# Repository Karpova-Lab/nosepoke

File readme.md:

# Nosepoke

Full Documentation here: [https://karpova-lab.github.io/nosepoke/](https://karpova-lab.github.io/nosepoke/)

Ask questions here: [https://github.com/Karpova-Lab/nosepoke/discussions](https://github.com/Karpova-Lab/nosepoke/discussions)

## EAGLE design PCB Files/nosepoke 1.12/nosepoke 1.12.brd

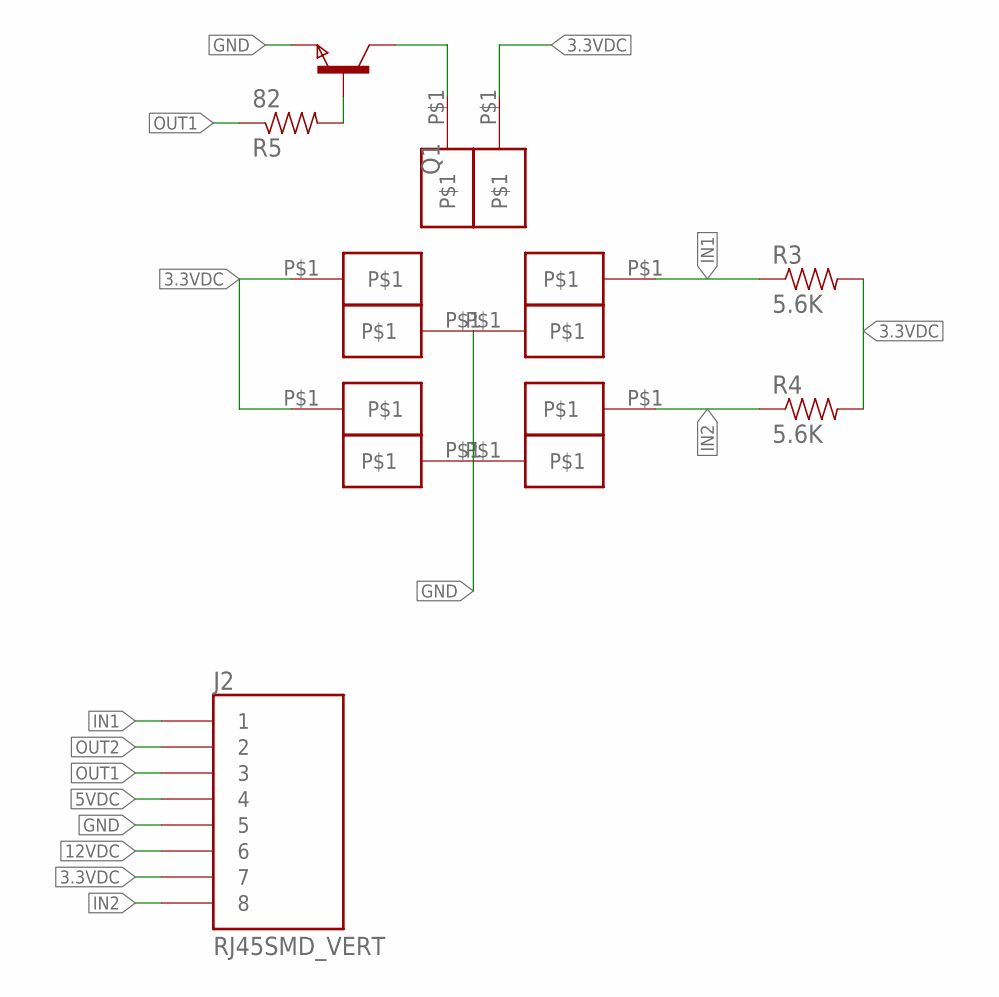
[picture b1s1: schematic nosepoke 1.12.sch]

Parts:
J2: RJ45SMD_VERT; RJ45_SMD_VERT
Q1: NPNSOT323; SOT323
R3, R4: 5.6K; 0805
R5: 82; 0805
U$1, U$2, U$3, U$4, U$5, U$6, U$7, U$8, U$9, U$10: PAD

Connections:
3.3VDC: J2.7, R3.2, R4.2, U$3.P$1, U$6.P$1, U$10.P$1
5VDC: J2.4
12VDC: J2.6
GND: J2.5, Q1.3 (E), U$1.P$1, U$2.P$1, U$5.P$1, U$8.P$1
IN1: J2.1, R3.1, U$7.P$1
IN2: J2.8, R4.1, U$4.P$1
unnamed: Q1.2 (B), R5.2
unnamed: Q1.1 (C), U$9.P$1
OUT1: J2.3, R5.1
OUT2: J2.2

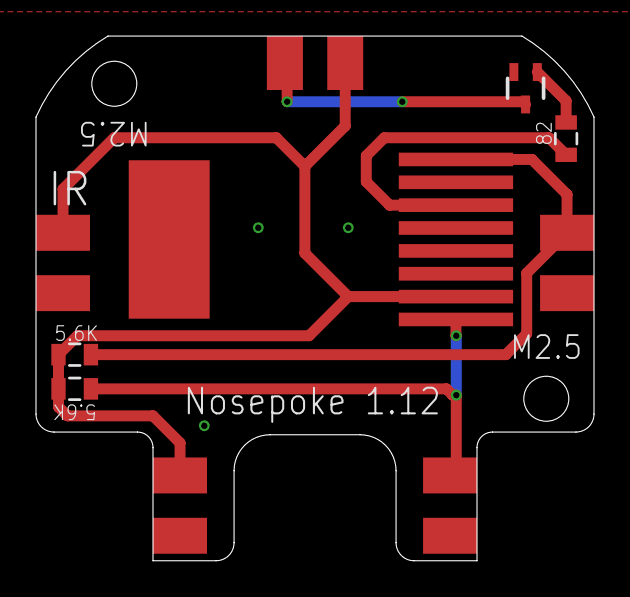
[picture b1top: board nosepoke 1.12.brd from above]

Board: 2 copper layers, 31.0 x 29.1 mm, 15 parts (0 on the bottom side), 7 nets.

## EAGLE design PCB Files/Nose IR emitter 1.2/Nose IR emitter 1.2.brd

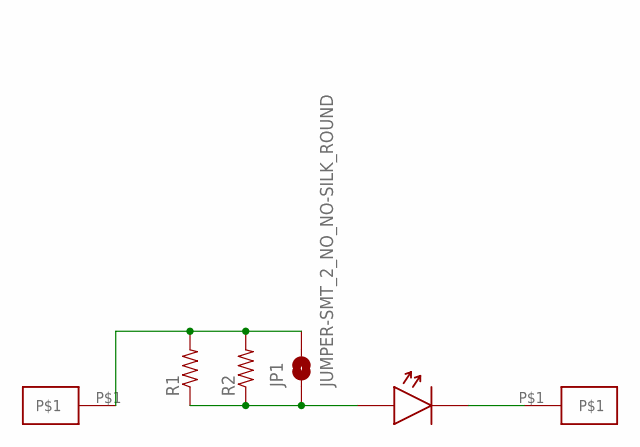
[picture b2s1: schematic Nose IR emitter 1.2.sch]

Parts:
JP1: JUMPER-SMT_2_NO_NO-SILK_ROUND; SMT-JUMPER_2_NO_NO-SILK_ROUND
R1, R2: RESISTOR0805-RES; 0805
U$1: IR_EMITTER
U$2, U$3: PAD

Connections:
unnamed: JP1.1, R1.1, R2.1, U$1.ANODE
unnamed: U$1.CATHODE, U$3.P$1
unnamed: JP1.2, R1.2, R2.2, U$2.P$1

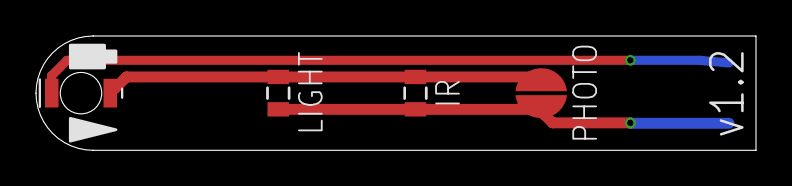
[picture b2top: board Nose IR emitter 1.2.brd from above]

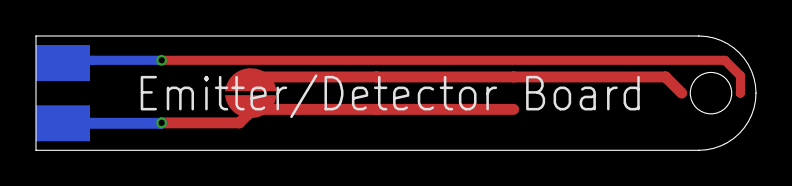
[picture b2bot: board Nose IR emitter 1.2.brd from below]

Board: 2 copper layers, 40.0 x 6.3 mm, 6 parts (2 on the bottom side), 3 nets.

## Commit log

2019-01-04 fixed broken CAD file links
2019-01-17 Doc update
2019-03-28 Documentation update
2019-12-11 Added readme with new licenses
2020-01-13 preparing to add kicad project
2020-04-13 Update to pyControl compatible nosepoke. Plastic body is shorter. No longer have lick detection. New shorter PCBs, designed in KiCAD. Big documentation update.
2020-04-13 readme update
2020-04-14 temp delete
2020-04-14 image link fix
2020-04-14 fix doc pcb images
2020-04-27 Improved assembly instructions with pictures.
2020-04-27 fixed missing picture
2020-06-17 fixed broken ibom link
2021-03-17 rear pcb v1.16
2021-06-03 transition to hugo
2021-06-03 added nosepoke aligner
2021-06-08 css updates
2021-06-10 images are can now be clicked to enlarge
2021-06-11 doc theme updates
2021-06-22 pictures added to doc overview
2021-06-22 fixed broken image links
2021-06-22 rearranged docs. added BOM and design files section
2021-06-22 fixed broken assembly image links
2022-10-13 backside PCB v1.17
2022-10-13 doc updates for PCB v1.17
2023-01-12 updated hugo theme submodule
2023-01-12 R1 link in docs now points to a 200Ω resistor on digikey
    fixes https://github.com/Karpova-Lab/nosepoke/issues/2
2023-07-18 fixed broken image link
2023-08-28 updated example task

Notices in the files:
parts and their libraries:
SparkFun-Jumpers: Licensing: Creative Commons ShareAlike 4.0 International - https://creativecommons.org/licenses/by-sa/4.0
